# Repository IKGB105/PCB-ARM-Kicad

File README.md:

# ARM Processor PCB Design (KiCad)

PCB design for an ARM-based board ("ArmVaquita"), from schematic capture through component placement and trace routing, built in KiCad.

## What's in this repo

- `ArmVaquita.kicad_pro` / `.kicad_pcb` — earlier board revision
- `Placa routeada/` — final routed version (`PLACAROUTEADA.kicad_pcb`), fully routed with copper pours and vias
- `Plot/` — exported Gerber/drill files, ready for fabrication

## Board features

- ARM Cortex-M MCU in QFP package as the central component
- USB connector for power/programming
- 4 user pushbuttons + reset button
- 8 status LEDs
- Multiple expansion headers (BOOT, camera interface, general I/O)
- Full 2-layer routing with ground pour

The 3D render above was generated directly from the routed board file with `kicad-cli pcb render`.

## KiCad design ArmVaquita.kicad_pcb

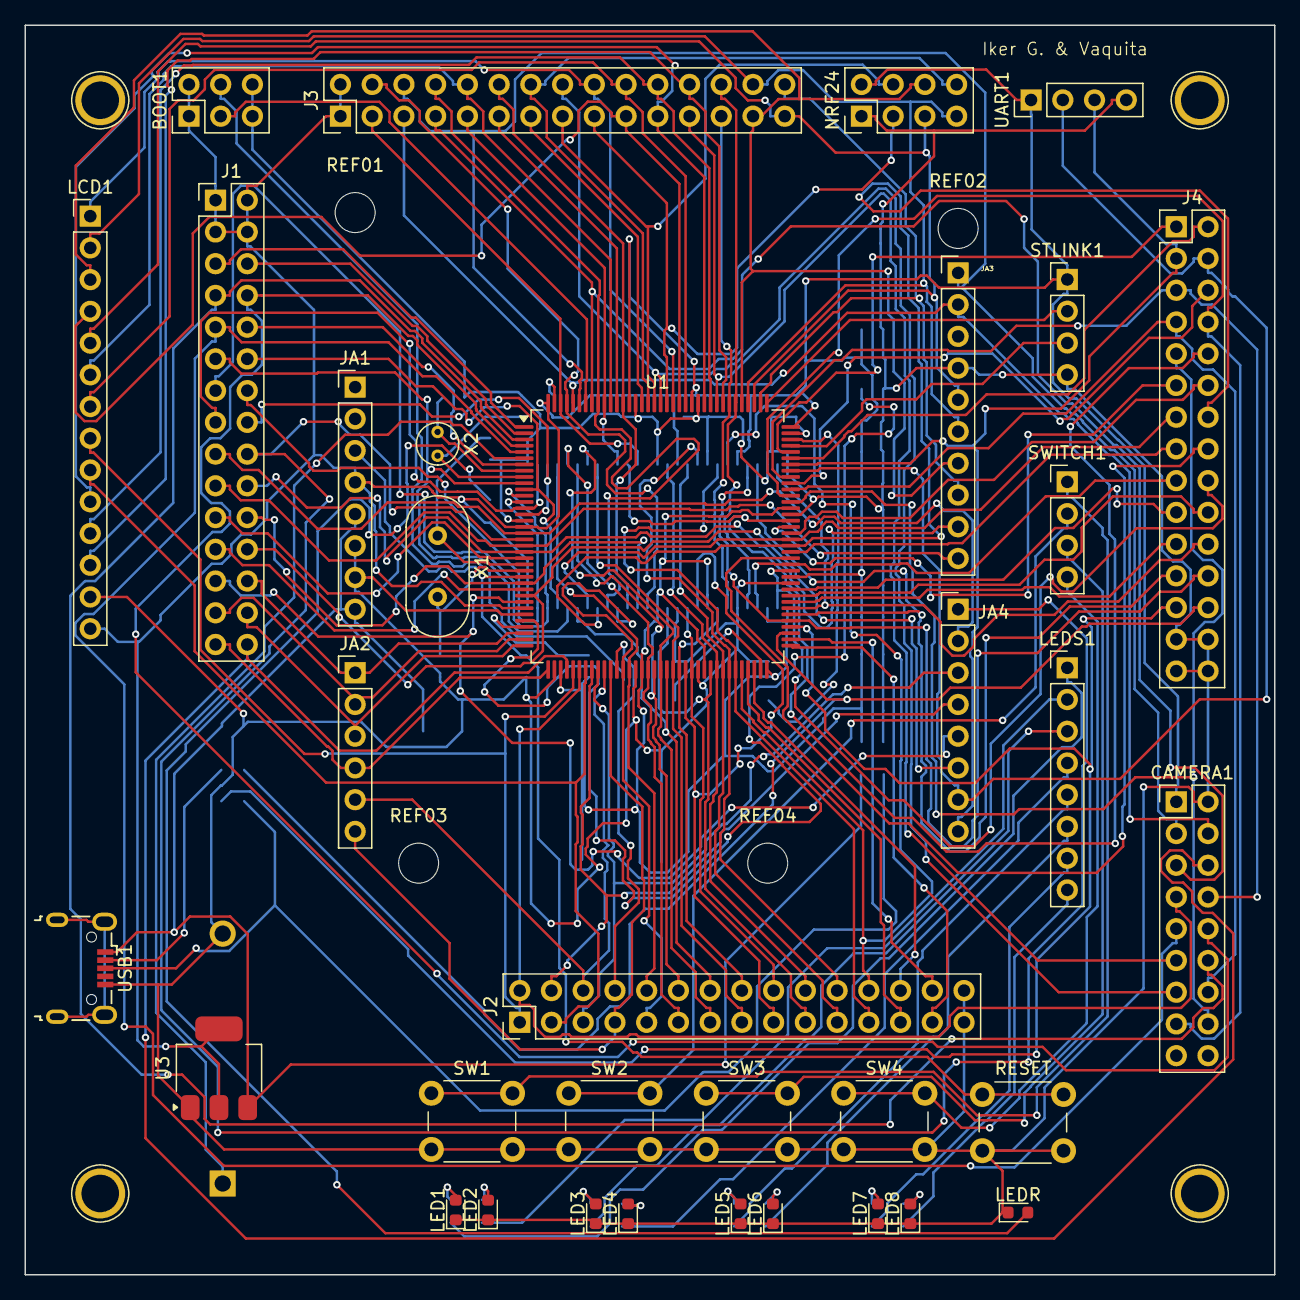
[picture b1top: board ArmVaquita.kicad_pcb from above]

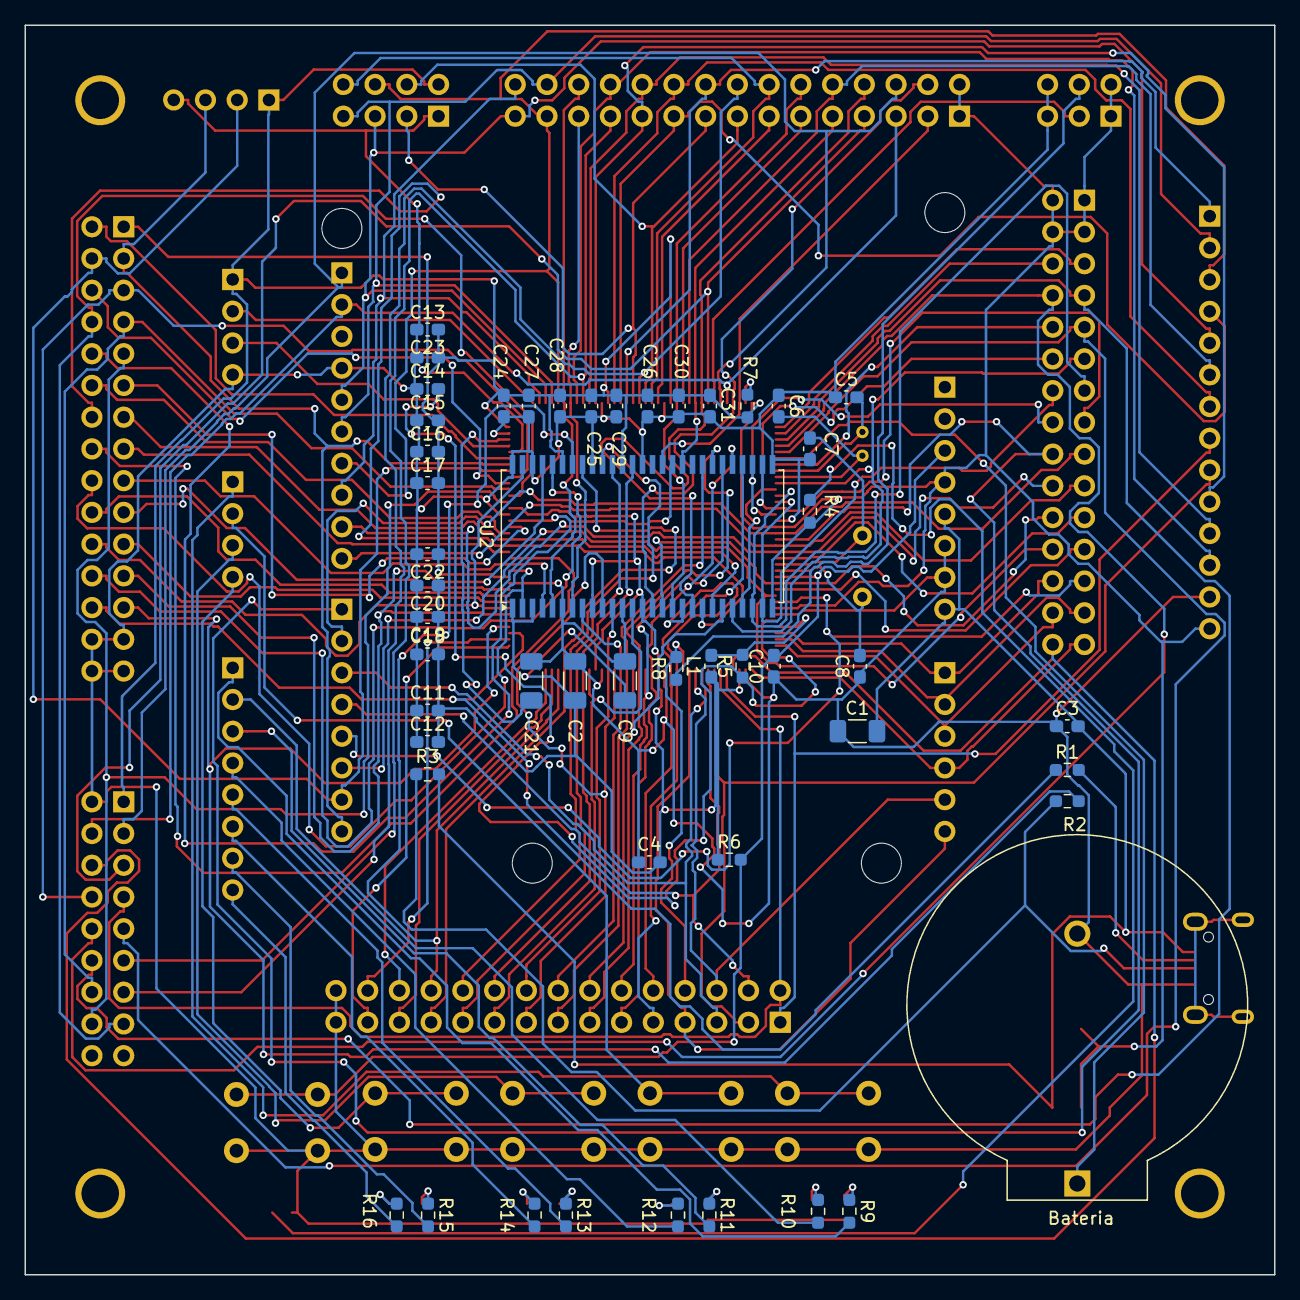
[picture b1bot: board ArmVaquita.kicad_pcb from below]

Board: 2 copper layers, 100.0 x 100.0 mm, 93 parts (51 on the bottom side), 149 nets.

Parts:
BOOT1: Conn2x3; PinHeader_2x03_P2.54mm_Vertical
Bateria: Portapila; BatteryHolder_ComfortableElectronic_CH273-2450_1x2450
C1, C2: 10uF; C_1206_3216Metric_Pad1.33x1.80mm_HandSolder
C3, C4, C10, C11, C12, C13, C14, C15, C16, C17, C18, C19, C20, C22, C23, C24, C25, C26, C27, C28, C29, C30, C31: 100nF; C_0603_1608Metric_Pad1.08x0.95mm_HandSolder
C5, C6: 12pF; C_0603_1608Metric_Pad1.08x0.95mm_HandSolder
C7, C8: 8pF; C_0603_1608Metric_Pad1.08x0.95mm_HandSolder
C9, C21: 2.2uF; C_1206_3216Metric_Pad1.33x1.80mm_HandSolder
CAMERA1: Conn2x9; PinHeader_2x09_P2.54mm_Vertical
Hoyo1: T#1; TestPoint_Plated_Hole_D3.0mm
Hoyo2: T#4; TestPoint_Plated_Hole_D3.0mm
Hoyo3: T#3; TestPoint_Plated_Hole_D3.0mm
Hoyo4: T#2; TestPoint_Plated_Hole_D3.0mm
J1, J3, J4: Conn2x15; PinHeader_2x15_P2.54mm_Vertical
J2: Con2x15; PinHeader_2x15_P2.54mm_Vertical
JA1, JA4: HDR1X8; PinHeader_1x08_P2.54mm_Vertical
JA2: HDR1X6; PinHeader_1x06_P2.54mm_Vertical
JA3: HDR1X10; PinHeader_1x10_P2.54mm_Vertical
L1: 10uH; L_0603_1608Metric_Pad1.05x0.95mm_HandSolder
LCD1: Conn1x14; PinHeader_1x14_P2.54mm_Vertical
LED1, LED2, LED3, LED4, LED5, LED6, LED7, LED8: AZUL; LED_0603_1608Metric
LEDR: ROJO; LED_0603_1608Metric
LEDS1: Conn1x8; PinHeader_1x08_P2.54mm_Vertical
NRF24: Conn2x4; PinHeader_2x04_P2.54mm_Vertical
R1, R2: 22; R_0603_1608Metric_Pad0.98x0.95mm_HandSolder
R3, R6, R8: 10k; R_0603_1608Metric_Pad0.98x0.95mm_HandSolder
R4, R9, R10, R11, R12, R13, R14, R15, R16: 220; R_0603_1608Metric_Pad0.98x0.95mm_HandSolder
R5, R7: 0; R_0603_1608Metric_Pad0.98x0.95mm_HandSolder
REF01, REF02, REF03, REF04: MountingHole; MountingHole_3.2mm_M3_DIN965
RESET: SW_Push; SW_PUSH_6mm_H4.3mm
STLINK1: Conn_01x04; PinHeader_1x04_P2.54mm_Vertical
SW1, SW2, SW3, SW4: SW_Push; SW_PUSH_6mm_H4.3mm
SWITCH1: Conn1x4; PinHeader_1x04_P2.54mm_Vertical
U1: STM32F446ZETx; LQFP-144_20x20mm_P0.5mm
U2: IS42S16400J-xT; TSOP-II-54_22.2x10.16mm_P0.8mm
U3: LM317_SOT-223; SOT-223-3_TabPin2
UART1: Conn1x4; PinHeader_1x04_P2.54mm_Vertical
USB1: USB_B_Mini; USB_Micro-B_Wuerth_629105150521
X1: 8MHz; Crystal_HC18-U_Vertical
X2: 32.768KHz; Crystal_C38-LF_D3.0mm_L8.0mm_Vertical

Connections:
+5V: C1.2, C3.2, JA1.5, JA1.8, R3.2, U3.3 (VI), USB1.1 (VBUS)
/8: C5.2, U1.8 (PC14), X2.1
/9: C6.2, U1.9 (PC15), X2.2
/23: C7.2, U1.23 (PH0), X1.1
/24: C8.2, U1.24 (PH1), X1.2
/32: C14.2, R5.1, U1.32 (VREF+)
/33: L1.2, R5.2, U1.33 (VDDA)
/71: C9.2, U1.71 (VCAP_1)
/106: C21.1, U1.106 (VCAP_2)
/BOOT0: BOOT1.3, U1.138 (BOOT0)
/BOOT1(PB2): J2.8, R8.2, U1.48 (PB2)
/PA0: J1.26, JA2.1, U1.34 (PA0)
/PA1: J1.27, JA2.2, U1.35 (PA1)
/PA2: J1.28, JA2.3, U1.36 (PA2)
/PA3: J1.29, JA2.4, U1.37 (PA3)
/PA4: CAMERA1.6, J1.30, U1.40 (PA4)
/PA5: J2.1, LCD1.8, U1.41 (PA5)
/PA6: CAMERA1.7, J2.2, U1.42 (PA6)
/PA7: J2.3, LCD1.9, U1.43 (PA7)
/PA8: CAMERA1.8, J4.5, U1.100 (PA8)
/PA9: J4.4, JA4.7, U1.101 (PA9), UART1.2
/PA10: J4.3, JA4.8, U1.102 (PA10), UART1.3
/PA11: J4.2, U1.103 (PA11)
/PA12: J4.1, U1.104 (PA12)
/PA15: J3.30, JA3.8, U1.110 (PA15)
/PB0: J2.6, JA2.5, U1.46 (PB0)
/PB1: J2.7, JA2.6, U1.47 (PB1)
/PB3: J3.11, U1.133 (PB3)
/PB4: J3.10, LCD1.6, U1.134 (PB4)
/PB5: J3.9, U1.135 (PB5), U2.37 (CKE)
/PB6: J3.8, U1.136 (PB6), U2.19 (~CS)
/PB7: CAMERA1.5, J3.7, U1.137 (PB7)
/PB8: CAMERA1.3, J3.6, JA3.1, U1.139 (PB8)
/PB9: CAMERA1.4, J3.5, JA3.2, U1.140 (PB9)
/PB10: J2.25, U1.69 (PB10)
/PB11: J2.26, U1.70 (PB11)
/PB12: J2.27, U1.73 (PB12)
/PB13: J2.28, U1.74 (PB13)
/PB14: J4.26, R1.1, U1.75 (PB14)
/PB15: J4.25, R2.2, U1.76 (PB15)
/PC0: J1.22, U1.26 (PC0), U2.16 (~WE)
/PC1: J1.23, U1.27 (PC1)
/PC2: J1.24, JA4.6, U1.28 (PC2)
/PC3: J1.25, JA4.5, U1.29 (PC3)
/PC4: J2.4, JA4.4, U1.44 (PC4)
/PC5: J2.5, JA4.3, U1.45 (PC5)
/PC6: CAMERA1.16, J4.9, U1.96 (PC6)
/PC7: CAMERA1.15, J4.8, U1.97 (PC7)
/PC8: CAMERA1.14, J4.7, U1.98 (PC8)
/PC9: J4.6, U1.99 (PC9)
/PC10: J3.29, JA3.5, LCD1.5, NRF24.5, U1.111 (PC10)
/PC11: J3.28, JA3.6, LCD1.2, NRF24.7, U1.112 (PC11)
/PC12: J3.27, JA3.7, LCD1.3, NRF24.6, U1.113 (PC12)
/PC13: J1.10, U1.7 (PC13)
/PD0: J3.26, U1.114 (PD0), U2.5 (DQ2)
/PD1: J3.25, U1.115 (PD1), U2.7 (DQ3)
/PD2: J3.24, LCD1.12, U1.116 (PD2)
/PD3: CAMERA1.11, J3.23, U1.117 (PD3)
/PD4: J3.22, LCD1.11, U1.118 (PD4)
/PD5: J3.21, LCD1.10, U1.119 (PD5)
/PD6: J3.20, LCD1.7, U1.122 (PD6)
/PD7: J3.19, LCD1.4, U1.123 (PD7)
/PD8: J4.24, U1.77 (PD8), U2.50 (DQ13)
/PD9: J4.23, U1.78 (PD9), U2.51 (DQ14)
/PD10: J4.22, U1.79 (PD10), U2.53 (DQ15)
/PD11: J4.21, U1.80 (PD11)
/PD12: J4.20, U1.81 (PD12)
/PD13: J4.19, U1.82 (PD13)
/PD14: J4.18, U1.85 (PD14), U2.2 (DQ0)
/PD15: J4.17, U1.86 (PD15), U2.4 (DQ1)
/PE0: J3.4, U1.141 (PE0), U2.15 (LDQM)
/PE1: J3.3, U1.142 (PE1), U2.39 (UDQM)
/PE2: J1.5, U1.1 (PE2)
/PE3: J1.6, U1.2 (PE3)
/PE4: CAMERA1.12, J1.7, U1.3 (PE4)
/PE5: CAMERA1.10, J1.8, U1.4 (PE5)
/PE6: CAMERA1.9, J1.9, U1.5 (PE6)
/PE7: J2.16, U1.58 (PE7), U2.8 (DQ4)
/PE8: J2.17, U1.59 (PE8), U2.10 (DQ5)
/PE9: J2.18, U1.60 (PE9), U2.11 (DQ6)
/PE10: J2.19, U1.63 (PE10), U2.13 (DQ7)
/PE11: J2.20, U1.64 (PE11), U2.42 (DQ8)
/PE12: J2.21, U1.65 (PE12), U2.44 (DQ9)
/PE13: J2.22, U1.66 (PE13), U2.45 (DQ10)
/PE14: J2.23, U1.67 (PE14), U2.47 (DQ11)
/PE15: J2.24, U1.68 (PE15), U2.48 (DQ12)
/PF0: J1.11, U1.10 (PF0), U2.23 (A0)
/PF1: J1.12, U1.11 (PF1), U2.24 (A1)
/PF2: J1.13, U1.12 (PF2), U2.25 (A2)
/PF3: J1.14, U1.13 (PF3), U2.26 (A3)
/PF4: J1.15, U1.14 (PF4), U2.29 (A4)
/PF5: J1.16, U1.15 (PF5), U2.30 (A5)
/PF6: J1.17, JA4.2, U1.18 (PF6)
/PF7: J1.18, JA4.1, U1.19 (PF7)
/PF8: J1.19, JA3.10, U1.20 (PF8)
/PF9: J1.20, JA3.9, U1.21 (PF9)
/PF10: J1.21, U1.22 (PF10)
/PF11: J2.9, U1.49 (PF11), U2.18 (~RAS)
/PF12: J2.10, U1.50 (PF12), U2.31 (A6)
/PF13: J2.11, U1.53 (PF13), U2.32 (A7)
/PF14: J2.12, U1.54 (PF14), U2.33 (A8)
/PF15: J2.13, U1.55 (PF15), U2.34 (A9)
/PG0: J2.14, U1.56 (PG0), U2.22 (A10)
/PG1: J2.15, U1.57 (PG1), U2.35 (A11)
/PG2: J4.16, U1.87 (PG2)
/PG3: J4.15, U1.88 (PG3)
/PG4: J4.14, U1.89 (PG4), U2.20 (BA0)
/PG5: J4.13, U1.90 (PG5), U2.21 (BA1)
/PG6: J4.12, U1.91 (PG6)
/PG7: J4.11, U1.92 (PG7)
/PG8: J4.10, U1.93 (PG8), U2.38 (CLK)
/PG9: J3.18, LCD1.1, U1.124 (PG9)
/PG10: J3.17, NRF24.3, U1.125 (PG10)
/PG11: CAMERA1.13, J3.16, U1.126 (PG11)
/PG12: J3.15, NRF24.4, U1.127 (PG12)
/PG13: J3.14, NRF24.8, U1.128 (PG13)
/PG14: J3.13, U1.129 (PG14)
/PG15: J3.12, U1.132 (PG15), U2.17 (~CAS)
/RES: C10.2, JA1.3, R6.2, RESET.2, U1.25 (NRST)
/SWCLK: STLINK1.2, U1.109 (PA14)
/SWDIO: STLINK1.3, U1.105 (PA13)
/VBAT: Bateria.1, U1.6 (VBAT)
Earth: BOOT1.5, BOOT1.6, Bateria.2, C1.1, C2.1, C3.1, C4.1, C5.1, C6.1, C7.1, C8.1, C9.1, C10.1, C11.1, C12.1, C13.1, C14.1, C15.1, C16.1, C17.1, C18.1, C19.2, C20.2, C21.2, C22.2, C23.2, C24.2, C25.2, C26.1, C27.1, C28.1, C29.2, C30.2, C31.2, CAMERA1.2, J2.29, J2.30, J4.27, J4.28, J4.29, J4.30, JA1.6, JA1.7, JA3.4, LCD1.13, LED1.1 (K), LED2.1 (K), LED3.1 (K), LED4.1 (K), LED5.1 (K), LED6.1 (K), LED7.1 (K), LED8.1 (K), LEDR.1 (K), NRF24.1, RESET.1, STLINK1.4, SW1.2, SW2.2, SW3.2, SW4.2, U1.16 (VSS), U1.31 (VSSA), U1.38 (VSS), U1.51 (VSS), U1.61 (VSS), U1.83 (VSS), U1.94 (VSS), U1.107 (VSS), U1.120 (VSS), U1.130 (VSS), U2.6 (GNDQ), U2.12 (GNDQ), U2.28 (GND), U2.41 (GND), U2.46 (GNDQ), U2.52 (GNDQ), U2.54 (GND), U3.1 (ADJ), UART1.4, USB1.5 (GND)
unnamed: BOOT1.4, R8.1
unnamed: LED1.2 (A), R9.1
unnamed: LED2.2 (A), R10.1
unnamed: LED3.2 (A), R11.1
unnamed: LED4.2 (A), R12.1
unnamed: LED5.2 (A), R13.1
unnamed: LED6.2 (A), R14.1
unnamed: LED7.2 (A), R15.1
unnamed: LED8.2 (A), R16.1
unnamed: LEDR.2 (A), R4.2
unnamed: LEDS1.1, R9.2
unnamed: LEDS1.2, R10.2
unnamed: LEDS1.3, R11.2
unnamed: LEDS1.4, R12.2
unnamed: LEDS1.5, R13.2
unnamed: LEDS1.6, R14.2
unnamed: LEDS1.7, R15.2
unnamed: LEDS1.8, R16.2
unnamed: SW1.1, SWITCH1.1
unnamed: SW2.1, SWITCH1.2
unnamed: SW3.1, SWITCH1.3
unnamed: SW4.1, SWITCH1.4
unnamed: R7.2, U1.143 (PDR_ON)
unnamed: R2.1, R3.1, USB1.3 (D+)
unnamed: R1.2, USB1.2 (D-)
VDD: BOOT1.1, BOOT1.2, C2.2, C4.2, C11.2, C12.2, C13.2, C15.2, C16.2, C17.2, C18.2, C19.1, C20.1, C22.1, C23.1, C24.1, C25.1, C26.2, C27.2, C28.2, C29.1, C30.1, C31.1, CAMERA1.1, J1.1, J1.2, J1.3, J1.4, J3.1, J3.2, JA1.4, L1.1, LCD1.14, NRF24.2, R4.1, R6.1, R7.1, STLINK1.1, U1.17 (VDD), U1.30 (VDD), U1.39 (VDD), U1.52 (VDD), U1.62 (VDD), U1.72 (VDD), U1.84 (VDD), U1.95 (VDDUSB), U1.108 (VDD), U1.121 (VDD), U1.131 (VDD), U1.144 (VDD), U2.1 (VDD), U2.3 (VDDQ), U2.9 (VDDQ), U2.14 (VDD), U2.27 (VDD), U2.43 (VDDQ), U2.49 (VDDQ), U3.2 (VO), UART1.1
